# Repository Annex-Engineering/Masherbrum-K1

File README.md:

# Masherbrum (K1) Printer

## Please Note: As of 04-09-2024, The Final Release of K1 is: Release 3 for XY Gantry and Release 2.2 for Z Drive, What you See is What you Get

## Info:
Project Masherbrum (K1 for short) is a Medium Format, Direct Drive, Fully Enclosed FDM Printer.

This is an entirely scratch design, based on the efforts of the "Hypercube Overkill Project" for the XY Motion System, and inspired by all other prior repraps.

Our discord server can be found here: 

BOM/Sourcing Guide for a 250x250x250 Build can be found here: https://docs.google.com/spreadsheets/d/1O3eyVuQ6M4F03MJSDs4Z71_XyNjXL5HFTZr1jsaAtRc/edit?usp=sharing

Frame Calculator: https://docs.google.com/spreadsheets/d/1OafYgwpRugKy69tp4yEFCRedxJVDkKtnEzjKQJuyjoY/edit?usp=sharing

## Stats:
- Fully Enclosed Design
- 2020, 2040, and 4040 Frame Members
- Insulated Build Chamber (Not Heated)
- Build Volumes of ~200^3 to 500^3 (use of whole plate available) + additional area to purge and wipe
     - Z can theoretically be 1m tall, just not fully supported or tested

- Direct Drive Extruder (Sherpa Mini)

- Shortest Belt Paths Possible, 4 Motors, 2 Per X, 2 Per Y Axis
- Moving Gantry, Fixed Bed

- MGN12H Rails for XY Stationary Rails
- MGN15H Rails for XY Cross (Moving Members)
- MGN15H Rails for Z
- Laser cut and machined metal parts throughout for stiffness and strength (steel recommended in most places, aluminum on moving components)
- 20mm 2GT Belts on XY Motion 
- 20mm 2GT Belts with 20:1 Worm Drive on Z to lift the Bed 
- Heavy Duty Bearings
- NEMA17 Motors XYZ

- Minimal Printed Parts (ASA Required, PC Recommended for motion components)

- Fysetc Spider or S6 Controller + BTT Expander Board with Klipper Required
- Mosquito Style, Dragon Style, Mosquito Magnum+, Nitram's VolcoMosquito, and many other hotends supported
- 24V Power Standard, 48V Optional and Preferred
- Mains Bed

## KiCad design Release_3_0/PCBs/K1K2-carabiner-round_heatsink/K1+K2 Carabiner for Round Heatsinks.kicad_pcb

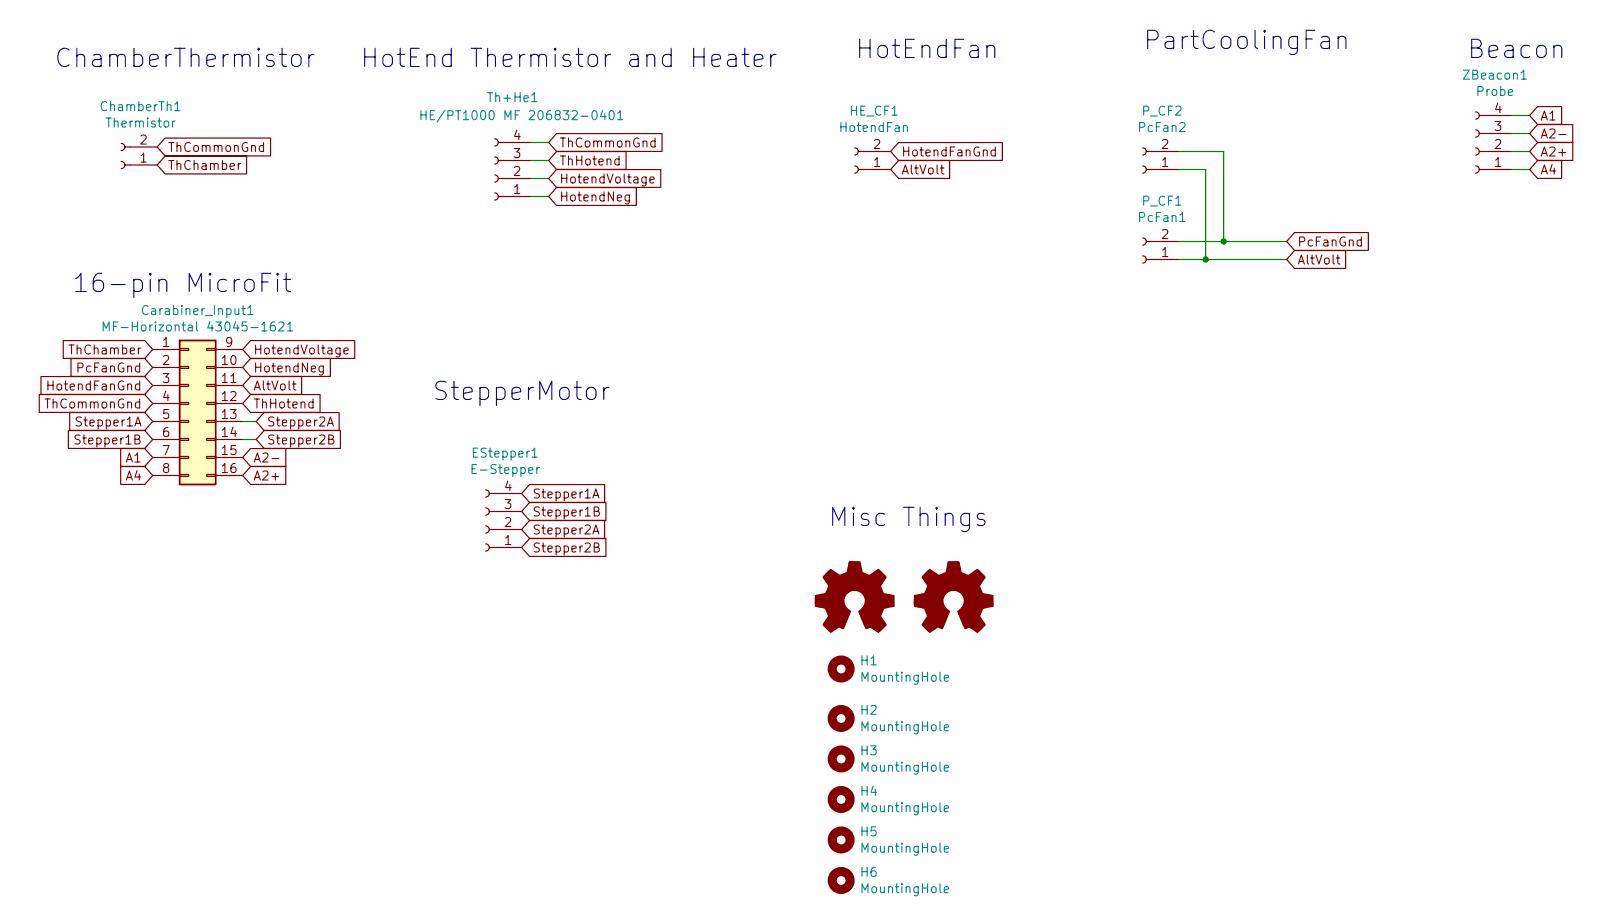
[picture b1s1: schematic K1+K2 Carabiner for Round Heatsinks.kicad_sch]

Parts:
Carabiner_Input1: MF-Horizontal 43045-1621; Molex_Micro-Fit_3.0_43045-1600_2x08_P3.00mm_Horizontal
ChamberTh1: Thermistor; 0603_to_1206_THT
EStepper1: E-Stepper; JST_XH_B4B-XH-A_1x04_P2.50mm_Vertical
H1, H2: MountingHole; MountingHole_4.5mm_Pad
H3, H4, H5, H6: MountingHole; MountingHole_3.5mm_Pad
HE_CF1: HotendFan; JST_XH_B2B-XH-A_1x02_P2.50mm_Vertical
LOGO1, LOGO2: Logo_Open_Hardware_Small; AnnexLogoFSilk
P_CF1: PcFan1; JST_XH_B2B-XH-A_1x02_P2.50mm_Vertical
P_CF2: PcFan2; JST_XH_B2B-XH-A_1x02_P2.50mm_Vertical
Th+He1: HE/PT1000 MF 206832-0401; Molex_Micro-Fit_3.0_43045-0412_2x02_P3.00mm_Vertical
ZBeacon1: Probe; JST_XH_B4B-XH-A_1x04_P2.50mm_Vertical

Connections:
A1: Carabiner_Input1.7, ZBeacon1.4
A2+: Carabiner_Input1.16, ZBeacon1.2
A2-: Carabiner_Input1.15, ZBeacon1.3
A4: Carabiner_Input1.8, ZBeacon1.1
AltVolt: Carabiner_Input1.11, HE_CF1.1, P_CF1.1, P_CF2.1
HotendFanGnd: Carabiner_Input1.3, HE_CF1.2
HotendNeg: Carabiner_Input1.10, Th+He1.1
HotendVoltage: Carabiner_Input1.9, Th+He1.2
PcFanGnd: Carabiner_Input1.2, P_CF1.2, P_CF2.2
Stepper1A: Carabiner_Input1.5, EStepper1.4
Stepper1B: Carabiner_Input1.6, EStepper1.3
Stepper2A: Carabiner_Input1.13, EStepper1.2
Stepper2B: Carabiner_Input1.14, EStepper1.1
ThChamber: Carabiner_Input1.1, ChamberTh1.1
ThCommonGnd: Carabiner_Input1.4, ChamberTh1.2, Th+He1.4
ThHotend: Carabiner_Input1.12, Th+He1.3

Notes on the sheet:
HotEndFan
Beacon
16-pin MicroFit
HotEnd Thermistor and Heater
StepperMotor
Misc Things
PartCoolingFan
ChamberThermistor

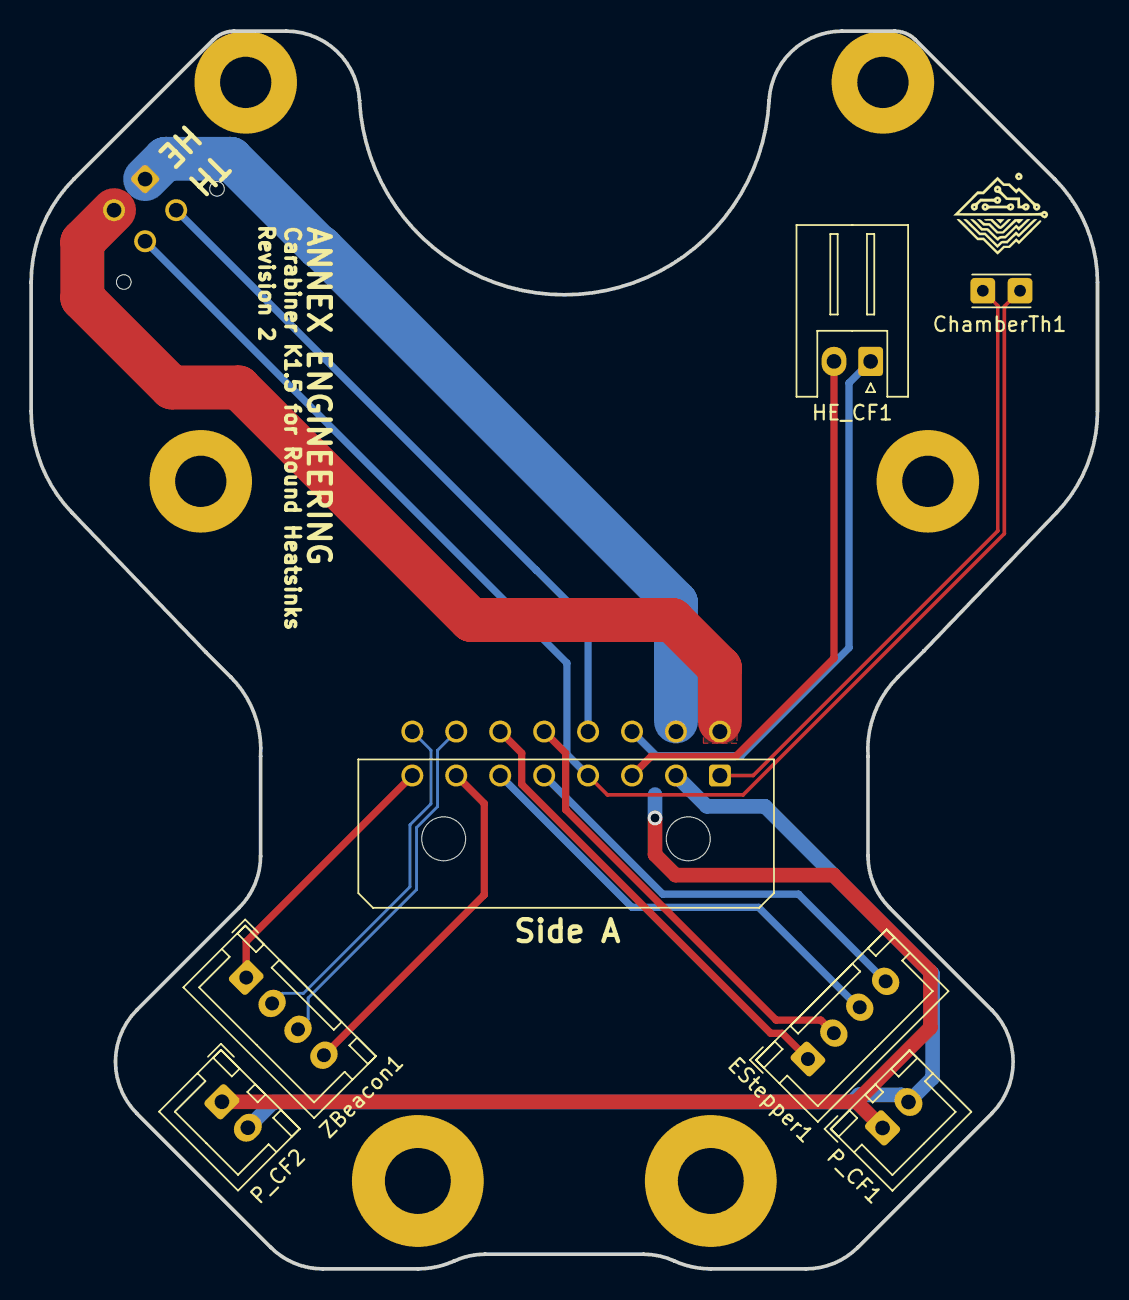
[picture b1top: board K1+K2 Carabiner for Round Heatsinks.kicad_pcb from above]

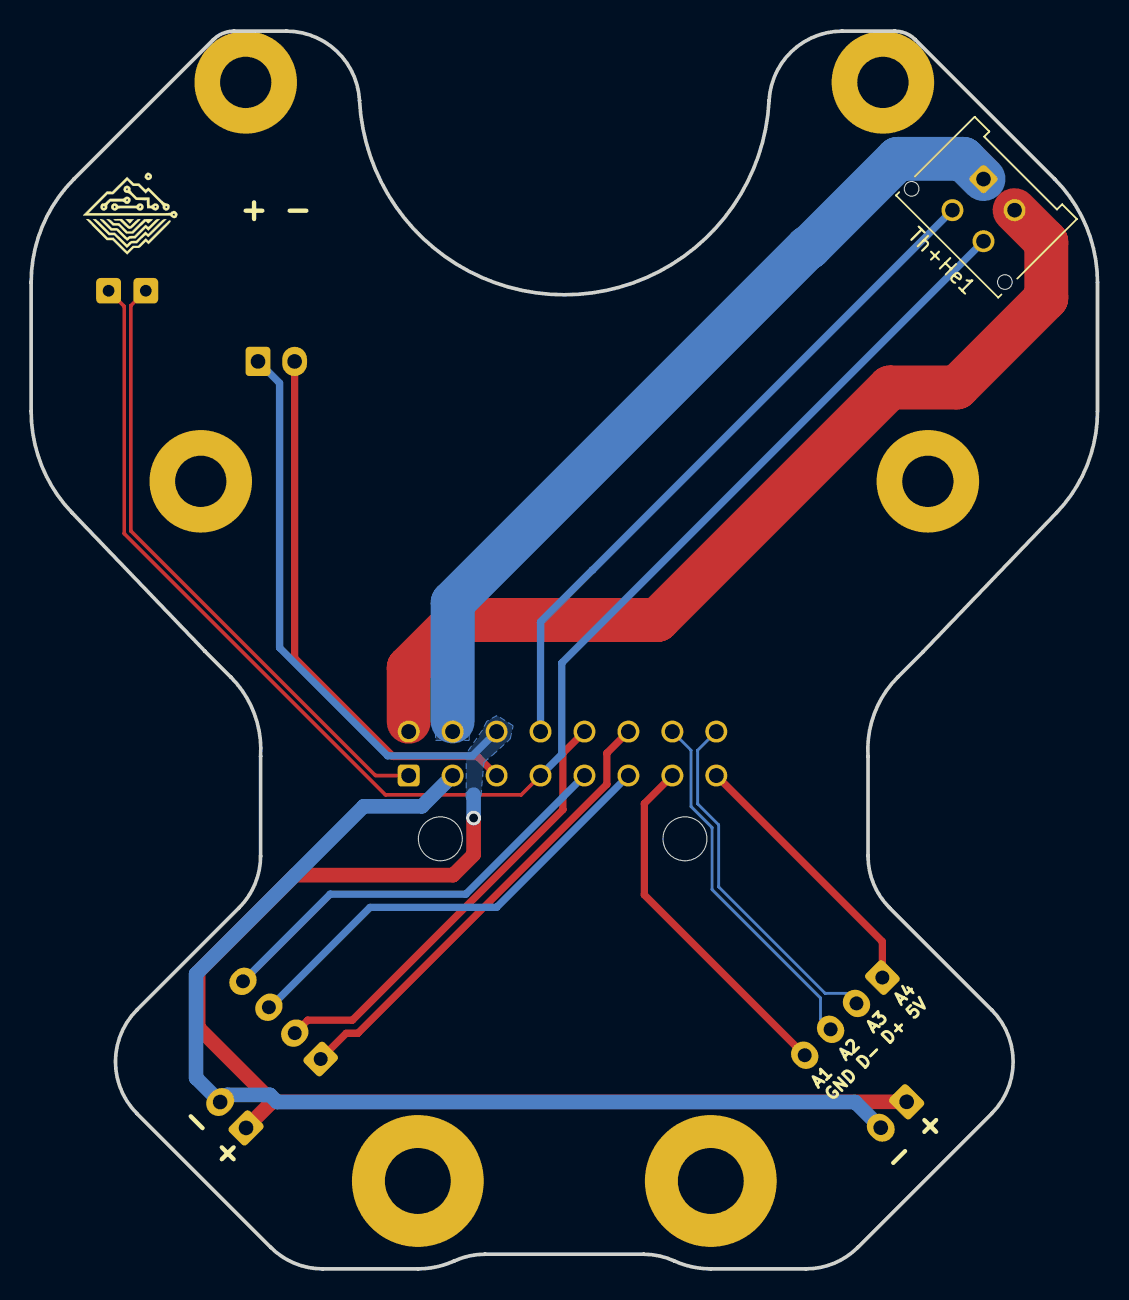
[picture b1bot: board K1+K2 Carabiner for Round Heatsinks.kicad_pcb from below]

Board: 2 copper layers, 72.8 x 84.5 mm, 16 parts (2 on the bottom side), 16 nets.

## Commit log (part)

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2020-03-05 fix incorrect pin definitions
    fix incorrect pin definitions
2020-03-08 rename pictures
2020-03-08 update edrawing
    update edrawing
2020-03-10 update edrawing
2020-03-11 replace dxfs for top panel to reference 45deg rotated nema17
2020-03-11 bolt in too from the underside, no more requirement to remove extruder to swap tool
2020-03-12 add front panel hinges
2020-03-16 add TL Dragon Hotend Holder
2020-03-18 add mosquito support
2020-03-24 add initial revision of BMG support to toolhead
    add initial revision of BMG support to toolhead
2020-03-25 add meanwell UHP-350-24 Mounting Bracket
    add meanwell UHP-350-24 Mounting Bracket
2020-03-27 add 24VDC wago block to model
2020-03-29 xy tower had m5 clearance hole, should have been m4 clearance hole
    xy tower had m5 clearance hole, should have been m4 clearance hole
2020-03-29 thicken walls of part cooling ducts, add flange to aid in printing
2020-03-31 remote sharp point from part cooling duct, printability
2020-04-02 tighten xy rail block, new z tower to more easily replace and remove nema17 motor
2020-04-02 extend nema17 main body by 4mm, too short. Fix wrong configuration xy rail holder
2020-04-04 solidify top cap, was too weak
2020-04-04 add sharp corner clearance to xy rail holder, stress relief
    add sharp corner clearance to xy rail holder, stress relief
2020-04-10 lighten/refactor mosquito mount
    supports 30 and 40mm fan with adapter, hotend rotated 90deg
2020-04-11 abs required
2020-04-14 remove duet toolboard mount, tweak length and clearance on cable anchor on x carriage, add magnet removal holes to probe pickup
2020-04-16 stiffen bmg mounting bracket
2020-04-19 dual xy switch drive tower support
2020-04-20 bmg only top plate release
    bmg only top plate release
2020-04-22 tighten rail install tool tolerances
2020-04-25 add experimental 16t drive/idler pulley support
    add experimental 16t drive/idler pulley support
2020-05-03 lightweight xy carriage version 2
    lightweight xy carriage version 2
2020-05-08 remove obsolete DXFs
2020-05-08 actually release correct back panel dxfs
    actually release correct back panel dxfs
2020-05-31 update xy carriage top plate to restore full xy travel, stiffen part by 15%
2020-06-18 re-add wiring retaining clips
2020-07-07 add reinforcing ribs to bmg top plate
    trying to stiffen tool mounting point in an effort to reduce low speed ringing
2020-07-09 add super_slicer profile
    add super_slicer profile
2020-07-09 add 400x400x600 build panels for socks
2020-07-28 add printed BF10 (bottom bearing) replacement block
    optional for now, requires 608 bearing
2020-07-28 add high flow variant of ducting (for pla, etc)
    add high flow variant of ducting (for pla, etc)
2020-07-29 Revert "revision 2 of high flow fan ducting"
    This reverts commit b893da2016b3b49f1eb4f00e1e900f2c8fcdbfb8.
2020-07-29 clean up fillets on chain anchors
2020-07-29 repair stl
2020-07-31 add oldham coupler style joint to z axis
    reduces chances of bent screws (especially if your on a budget) of affecting print quality
2020-08-04 high flow fan duct now standard
    high flow fan duct now standard
2020-08-06 oldham pockets werent set on layer multiples, move idler tower on xy 1mm forward for more motor clearance
    oldham pockets werent set on layer multiples, move idler tower on xy 1mm forward for more motor clearance
2020-08-06 prevent flat sections from appearing in oldham pockets
    prevent flat sections from appearing in oldham pockets
2020-08-13 add Meanwell LRS-200 and LRS-350 (and RSP) mounting bracket for converts from other machines
    add Meanwell LRS-200 and LRS-350 (and RSP) mounting bracket for converts from other machines
2020-08-14 reduce material usage in probe dock
2020-08-15 add folded ascender top plate
2020-08-20 xy idler endcaps allow bolt engagement into tnuts now
    xy idler endcaps allow bolt engagement into tnuts now
2020-08-26 update sherpa mini top plate to match release
    update sherpa mini top plate to match release
2020-08-27 add fysetc s6 + btt motor expander bracket, update skr bracket to match
    add fysetc s6 + btt motor expander bracket, update skr bracket to match
2020-08-28 update klipper config to match 08-16-2020 changes
2020-08-29 gantry was facing the wrong way
    i'm dumb
2020-08-30 tighten self taping region in new experimental z block_a's
    tighten self taping region in new experimental z block_a's
2020-09-02 FIRST REVISION OF THE ANNEX EULA
2020-09-03 fix print orientation on part
2020-09-14 add solid no oldham mounts (per socks request) for troubleshooting
2020-09-15 Update README.md
    Release Schedule:
    - Release 1 - RC2: Final True Release
    - Release 1: Bug Fixes from Final Testing of RC2
    - Release 1.1: Belted Z Drive Option
    - Release 1.2: New Front Door Design
    - Release 2.0: New Gantry
2020-09-15 Update README.md
    image link fixing
2020-09-16 rc2 prep
2020-10-04 add cad for fysetc s6 mounting frame, upon request
2020-10-05 add experimental bass fan ducts (super flow)
    i have no idea where this name came from
2020-10-21 add mgn12 and mgn15 rail install tools
2020-10-23 coupler needed additional clearance on drive tower
2020-10-29 add m3 inserts variant of electronics box corners
2020-11-04 neopixel changes
2020-11-09 add release 1.2 doors to repo
2020-11-13 release 2 - Pre-Alpha Preview
2020-11-16 move to double shear pin setup to support the belt
2020-11-16 update belted z edrawing
    update belted z edrawing
2020-11-17 add piton dragon mount
2020-11-17 add triple hinge variant for doors (completely optional)
2020-11-18 replace 10x3 CS piton with 6x3 flat magnet piton
2020-11-18 add skr1.4 config, fix minor typos on 1.3 config, remove old 1.3 code
2020-11-19 upload correct endcap
2020-11-21 add release 2 alpha
2020-11-22 add cable tie lances to xy main frame on alpha R2 carriage
2020-11-24 revise belted z motor towers to match actual production motors
2020-11-24 add theoretical wiring cover to toolhead
2020-11-25 fix motor key flange interference in motor mounts
2020-11-26 remove bridge on bottom plate, core out sections on main frame where extra materal is not required
2020-11-27 make part cooling transfer duct portion of parts a bit more printable
2020-11-29 add updated slicer profiles (with profiles from R2 benchy video)
2020-12-04 add mgn12c linear rail support to ballscrew z drive
2020-12-09 1.2 release
2020-12-09 add missing stls, dxfs and pdfs to release 2 folder
2020-12-11 add beta 2 piece ballscrew z mount to resist ejecting radial bearings
    to not use snap rings, were trying this, if this fails, snap rings it is
2020-12-16 update readme for R2
2020-12-19 add benchy racing profiles
2020-12-21 R2-Beta2 prep
    - remove nozzle switch/purge bucket combo
    - add pape purge bucket
    - add pape d2f probe
2020-12-26 add cad for purge and brush bucket
2020-12-31 uploaded wrong toolhead
2021-01-01 5020 fan pocket clearance
2021-01-02 minor printability improvements, alter fillet sizes around rear of part
2021-01-07 add 450 and 500mm doors
2021-01-08 typo in bmg rotation_distance
2021-01-08 add s6 2.0 config, fix pin issue on 1.2 config
2021-01-08 first pass, dockable r2 z probe config
2021-01-08 stated inductive, should be microswitch
2021-01-08 add 450^3 and 500^3 panels
2021-01-10 remove microsteps setting from tmc2209 blocks
2021-01-11 update edrawing, fix doors (off by 25mm width prior)
2021-01-15 retrofit r2 probe mount (your on your own)
2021-01-19 add draft to probe dock and probe housing to aid in entry when dock is slightly misaligned
2021-01-21 add bracing bolts to microswitch dock (optional)
2021-01-22 update ideamaker profiles, more temps, cleaner retractions, better support for 5020 fans
2021-01-23 first pass fan ducts for new bracing/probe setup
2021-01-26 add chungus fan ducting
2021-01-27 add belted z omc motor plates
2021-01-28 move release 1.2 to archive, update r2 configs to use updated macros
2021-01-31 convert R2 configs to use gear ratio
2021-02-06 ever so slight mounting hole shift for expander board
2021-02-20 add temp cad screenshots to github page
2021-03-11 add optional fysetc display housing edrawing and stls
2021-03-12 add toolhead cad for sherpa mini toolhead variant
2021-03-17 further material reduction from electronics box corner in an effort to reduce print time
2021-04-02 add actual sherpa mini to toolhead cad file
2021-04-05 add integrated 25mm fan mount
2021-04-16 klipper configs for 60:1 worm z
2021-04-19 clean up spool holder stuff
2021-04-27 slot motor mounting points
2021-05-12 rename files in prep for mag+ support
2021-05-22 worm drive bottom half strength improvements
2021-05-25 add extremely preliminary mag+ support (requires flipping the magswitch dock 180deg in the holder to work)
2021-05-27 better rpi brackets
2021-05-29 shorten stack height of rpi bracket to better fit on k3 printers
2021-05-30 add vertical variant of rs-25-5 bracket
2021-05-30 wrong orientation
2021-05-30 move skr and s6 v1.2 configs to legacy, update edrawing to use spider and btt expander
2021-05-30 add single s6 + btt motor expander configuration to github
2021-05-30 remove unused comments
2021-05-30 add spider + expander config
2021-05-30 bed mesh fade fix
2021-06-04 minor printability improvement to the bottom belted z idler
2021-06-11 R2 CAD
2021-06-14 move mag+ to experimental stls folder
2021-07-08 add mag+ probe dock mounting arm 1
2021-07-11 exported wrong file
2021-07-13 edrawings readme
2021-07-28 remove old and obsolete jigs
2021-07-31 add bosch extrusion variant of cable anchor
2021-08-04 homing retract distance = 0 on xy
2021-08-09 move planetaries and ballscrew z to deprecated folder
2021-08-11 2.0.1 compatible klipper config
2021-08-16 add experimental psu brackets
2021-08-19 tweak mag+ ducting to have better part cooling
2021-08-20 mirror rpi bracket
2021-08-31 add new z drive, 15mm belt only, mgn12c only
2021-09-07 update readme to signify 2.1 beta
2021-09-14 z tilt typo
2021-10-13 remove squash balls, move to amp feet
    thanks voron.....
2021-10-29 remove default parameters from config
2021-11-02 restore accidentally purged z drive to 2.0.1 archive folder
2021-11-02 remove squashball foot
2021-11-05 part orientation
2021-11-27 add k1 R2.1 cad to github
2021-11-28 add renders to 2.1 folder
2021-12-29 add rapido standard flow and UHF hotend support
2022-01-19 add 2.1.1 full frame edrawing
2022-01-20 add 4040 callout for gantry members on k1
2022-01-25 stls for 2040 k2 frame
2022-02-01 reorient print orientation for power supply brackets (per kmobs)
2022-02-09 add 0.4mm nozzle option
2022-02-16 dual uhp brackets
2022-02-26 first draft new electrical box
2022-02-27 m3 insert was 5mm, now 4.7mm hole
2022-02-28 easier to print fan guard
2022-03-02 add note about mentals dockable probe module being required
2022-03-22 fix missing fillet
2022-04-20 add T marker to top printed part, increase slot length from 6mm to 8mm on 15mm Z Drive
2022-04-29 prevent z idler position from rotating...ever
2022-05-06 Create Foot_to_frame_bracket_laser_panel_x4_rev1.STL
    Added Foot to frame bracket used in combination with lasercut bottom panel.
2022-06-01 2.2 to main
2022-11-09 release 3 concept edrawing of gantry only
2022-11-18 add rough 3.0 edrawing
2022-11-18 grommet tweaks for printability, color changes for filament usage balance
2022-11-18 more printable electronics box corners, now with less plastic
2022-12-01 r3 adjustments for clearance and shit
2022-12-11 make grommets easier to print and thread
2023-02-04 move beacon mount to 2.6mm from nozzle per recommendations
2023-04-04 R3 beta1 prep
2023-07-05 waterheater duct "final", remove qd2 support for now
2023-09-23 update bed to support tri-z
2023-10-06 pdfs for 4.0
